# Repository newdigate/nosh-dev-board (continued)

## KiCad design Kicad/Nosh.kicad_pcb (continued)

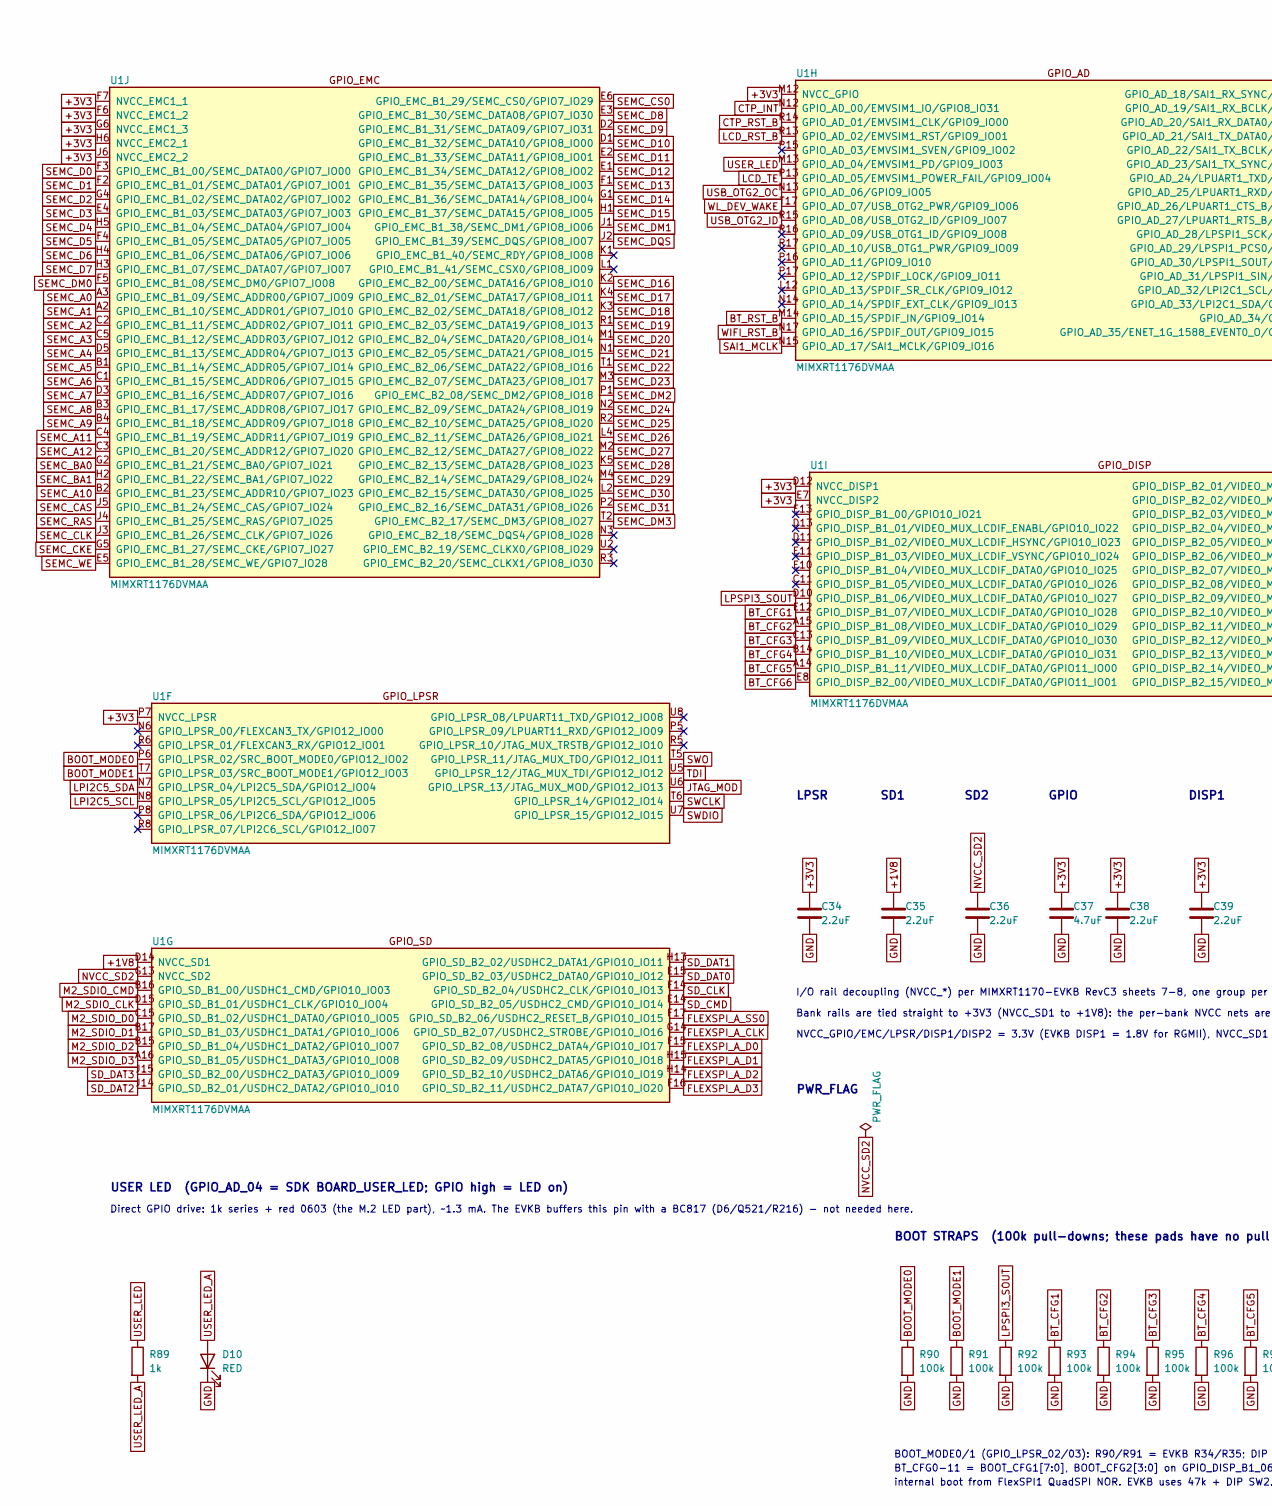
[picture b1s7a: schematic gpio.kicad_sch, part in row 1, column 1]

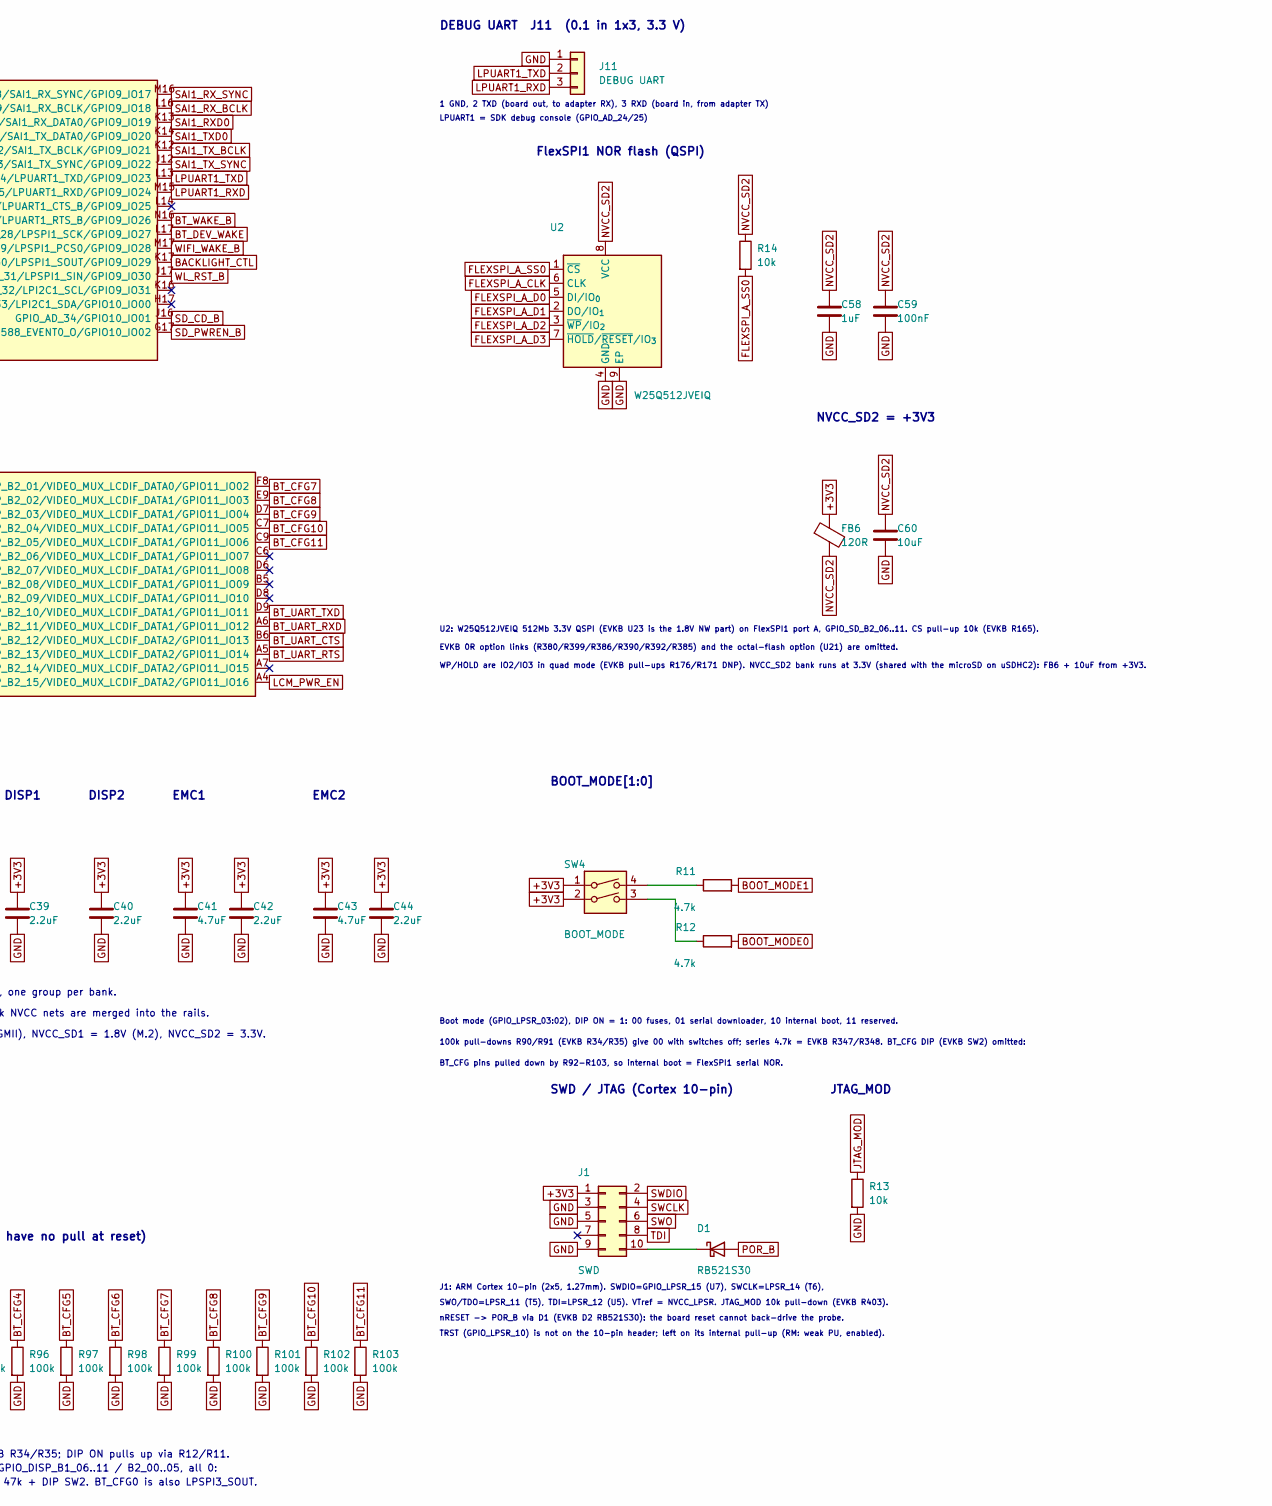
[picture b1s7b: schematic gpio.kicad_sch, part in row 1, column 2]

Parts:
C34, C35, C36, C38, C42, C44: 2.2uF; C_0402_1005Metric_ViP; MPN CL05A225MQ5NSNC; LCSC C12530
C37: 4.7uF; C_0402_1005Metric_ViP; MPN CL05A475MP5NRNC; LCSC C23733
C39, C40: 2.2uF; C_0402_1005Metric_JLC; MPN CL05A225MQ5NSNC; LCSC C12530
C41, C43: 4.7uF; C_0402_1005Metric_JLC; MPN CL05A475MP5NRNC; LCSC C23733
C58: 1uF; C_0402_1005Metric_JLC; MPN CL05A105KA5NQNC; LCSC C52923
C59: 100nF; C_0402_1005Metric_JLC; MPN CL05B104KO5NNNC; LCSC C1525
C60: 10uF; C_0603_1608Metric; MPN CL10A106KP8NNNC; LCSC C19702
D1: RB521S30; D_SOD-523; MPN RB521S30T1G; LCSC C145179
D10: RED; LED_0603_1608Metric; MPN KT-0603R; LCSC C2286
FB6: 120R; L_0402_1005Metric; MPN BLM15AG121SN1D; LCSC C85812
J1: SWD; PinHeader_2x05_P1.27mm_Vertical_SMD; MPN 20021121-00010C4LF; LCSC C150517
J11: DEBUG UART; PinHeader_1x03_P2.54mm_Vertical; MPN PZ254V-11-03P; LCSC C2937625
R11, R12: 4.7k; R_0402_1005Metric_JLC; MPN 0402WGF4701TCE; LCSC C25900
R13, R14: 10k; R_0402_1005Metric_JLC; MPN 0402WGF1002TCE; LCSC C25744
R89: 1k; R_0402_1005Metric_JLC; MPN 0402WGF1001TCE; LCSC C11702
R90, R91, R92, R93, R94, R95, R96, R97, R98, R99, R100, R101, R102, R103: 100k; R_0402_1005Metric_JLC; MPN 0402WGF1003TCE; LCSC C25741
SW4: BOOT_MODE; SW_DIP_SPSTx02_Slide_KingTek_DSHP02TS_W7.62mm_P1.27mm; MPN DSHP02TSGER; LCSC C3293142
U1: MIMXRT1176DVMAA; MAPBGA-289_14x14mm_Layout17x17_P0.8mm; MPN MIMXRT1176DVMAA; LCSC C1020237
U2: W25Q512JVEIQ; WSON-8-1EP_8x6mm_P1.27mm_EP3.4x4.3mm; MPN W25Q512JVEIQ; LCSC C7389628

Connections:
+1V8: C35.1, U1.D14 (NVCC_SD1); also elsewhere on the board
+3V3: C34.1, C37.1, C38.1, C39.1, C40.1, C41.1, C42.1, C43.1, C44.1, FB6.1, J1.1, SW4.1, SW4.2, U1.D12 (NVCC_DISP1), U1.E7 (NVCC_DISP2), U1.F6 (NVCC_EMC1_2), U1.F7 (NVCC_EMC1_1), U1.G6 (NVCC_EMC1_3), U1.H6 (NVCC_EMC2_1), U1.J6 (NVCC_EMC2_2), U1.M12 (NVCC_GPIO), U1.P7 (NVCC_LPSR); also elsewhere on the board
BACKLIGHT_CTL: U1.K17 (GPIO_AD_30/LPSPI1_SOUT/GPIO9_IO29); also elsewhere on the board
BOOT_MODE0: R12.2, R90.1, U1.P6 (GPIO_LPSR_02/SRC_BOOT_MODE0/GPIO12_IO02)
BOOT_MODE1: R11.2, R91.1, U1.T7 (GPIO_LPSR_03/SRC_BOOT_MODE1/GPIO12_IO03)
BT_CFG1: R93.1, U1.E12 (GPIO_DISP_B1_07/VIDEO_MUX_LCDIF_DATA0/G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)
BT_CFG2: R94.1, U1.A15 (GPIO_DISP_B1_08/VIDEO_MUX_LCDIF_DATA0/G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)
BT_CFG3: R95.1, U1.C13 (GPIO_DISP_B1_09/VIDEO_MUX_LCDIF_DATA0/G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)
BT_CFG4: R96.1, U1.B14 (GPIO_DISP_B1_10/VIDEO_MUX_LCDIF_DATA0/G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)
BT_CFG5: R97.1, U1.A14 (GPIO_DISP_B1_11/VIDEO_MUX_LCDIF_DATA0/G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)
BT_CFG6: R98.1, U1.E8 (GPIO_DISP_B2_00/VIDEO_MUX_LCDIF_DATA0/G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)
BT_CFG7: R99.1, U1.F8 (GPIO_DISP_B2_01/VIDEO_MUX_LCDIF_DATA0/G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)
BT_CFG8: R100.1, U1.E9 (GPIO_DISP_B2_02/VIDEO_MUX_LCDIF_DATA1/G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)
BT_CFG9: R101.1, U1.D7 (GPIO_DISP_B2_03/VIDEO_MUX_LCDIF_DATA1/G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)
BT_CFG10: R102.1, U1.C7 (GPIO_DISP_B2_04/VIDEO_MUX_LCDIF_DATA1/G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)
BT_CFG11: R103.1, U1.C9 (GPIO_DISP_B2_05/VIDEO_MUX_LCDIF_DATA1/G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)
BT_DEV_WAKE: U1.L17 (GPIO_AD_28/LPSPI1_SCK/GPIO9_IO27); also elsewhere on the board
BT_RST_B: U1.M14 (GPIO_AD_15/SPDIF_IN/GPIO9_IO14); also elsewhere on the board
BT_UART_CTS: U1.B6 (GPIO_DISP_B2_12/VIDEO_MUX_LCDIF_DATA2/G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); also elsewhere on the board
BT_UART_RTS: U1.A5 (GPIO_DISP_B2_13/VIDEO_MUX_LCDIF_DATA2/G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); also elsewhere on the board
BT_UART_RXD: U1.A6 (GPIO_DISP_B2_11/VIDEO_MUX_LCDIF_DATA1/G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); also elsewhere on the board
BT_UART_TXD: U1.D9 (GPIO_DISP_B2_10/VIDEO_MUX_LCDIF_DATA1/G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); also elsewhere on the board
BT_WAKE_B: U1.N16 (GPIO_AD_27/LPUART1_RTS_B/GPIO9_IO26); also elsewhere on the board
CTP_INT: U1.N12 (GPIO_AD_00/EMVSIM1_IO/GPIO8_IO31); also elsewhere on the board
CTP_RST_B: U1.R14 (GPIO_AD_01/EMVSIM1_CLK/GPIO9_IO00); also elsewhere on the board
FLEXSPI_A_CLK: U1.G14 (GPIO_SD_B2_07/USDHC2_STROBE/GPIO10_IO16), U2.6 (CLK)
FLEXSPI_A_D0: U1.F15 (GPIO_SD_B2_08/USDHC2_DATA4/GPIO10_IO17), U2.5 (DI/IO_{0})
FLEXSPI_A_D1: U1.H15 (GPIO_SD_B2_09/USDHC2_DATA5/GPIO10_IO18), U2.2 (DO/IO_{1})
FLEXSPI_A_D2: U1.H14 (GPIO_SD_B2_10/USDHC2_DATA6/GPIO10_IO19), U2.3 (~WP/IO_{2})
FLEXSPI_A_D3: U1.F16 (GPIO_SD_B2_11/USDHC2_DATA7/GPIO10_IO20), U2.7 (~HOLD/~RESET/IO_{3})
FLEXSPI_A_SS0: R14.2, U1.F17 (GPIO_SD_B2_06/USDHC2_RESET_B/GPIO10_IO15), U2.1 (~CS)
GND: C34.2, C35.2, C36.2, C37.2, C38.2, C39.2, C40.2, C41.2, C42.2, C43.2, C44.2, C58.2, C59.2, C60.2, D10.1 (K), J1.3, J1.5, J1.9, J11.1, R13.2, R90.2, R91.2, R92.2, R93.2, R94.2, R95.2, R96.2, R97.2, R98.2, R99.2, R100.2, R101.2, R102.2, R103.2, U2.4 (GND), U2.9 (EP); also elsewhere on the board
JTAG_MOD: R13.1, U1.U6 (GPIO_LPSR_13/JTAG_MUX_MOD/GPIO12_IO13)
LCD_RST_B: U1.R13 (GPIO_AD_02/EMVSIM1_RST/GPIO9_IO01); also elsewhere on the board
LCD_TE: U1.P13 (GPIO_AD_05/EMVSIM1_POWER_FAIL/GPIO9_IO04); also elsewhere on the board
LCM_PWR_EN: U1.A4 (GPIO_DISP_B2_15/VIDEO_MUX_LCDIF_DATA2/G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); also elsewhere on the board
LPI2C5_SCL: U1.N8 (GPIO_LPSR_05/LPI2C5_SCL/GPIO12_IO05); also elsewhere on the board
LPI2C5_SDA: U1.N7 (GPIO_LPSR_04/LPI2C5_SDA/GPIO12_IO04); also elsewhere on the board
LPSPI3_SOUT: R92.1, U1.D10 (GPIO_DISP_B1_06/VIDEO_MUX_LCDIF_DATA0/G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)
LPUART1_RXD: J11.3, U1.M15 (GPIO_AD_25/LPUART1_RXD/GPIO9_IO24)
LPUART1_TXD: J11.2, U1.L13 (GPIO_AD_24/LPUART1_TXD/GPIO9_IO23)
M2_SDIO_CLK: U1.D15 (GPIO_SD_B1_01/USDHC1_CLK/GPIO10_IO04); also elsewhere on the board
M2_SDIO_CMD: U1.B16 (GPIO_SD_B1_00/USDHC1_CMD/GPIO10_IO03); also elsewhere on the board
M2_SDIO_D0: U1.C15 (GPIO_SD_B1_02/USDHC1_DATA0/GPIO10_IO05); also elsewhere on the board
M2_SDIO_D1: U1.B17 (GPIO_SD_B1_03/USDHC1_DATA1/GPIO10_IO06); also elsewhere on the board
M2_SDIO_D2: U1.B15 (GPIO_SD_B1_04/USDHC1_DATA2/GPIO10_IO07); also elsewhere on the board
M2_SDIO_D3: U1.A16 (GPIO_SD_B1_05/USDHC1_DATA3/GPIO10_IO08); also elsewhere on the board
NVCC_SD2: C36.1, C58.1, C59.1, C60.1, FB6.2, R14.1, U1.G13 (NVCC_SD2), U2.8 (VCC); also elsewhere on the board
unnamed: D1.1 (K), J1.10
unnamed: R11.1, SW4.4
unnamed: R12.1, SW4.3
POR_B: D1.2 (A); also elsewhere on the board
SAI1_MCLK: U1.N15 (GPIO_AD_17/SAI1_MCLK/GPIO9_IO16); also elsewhere on the board
SAI1_RXD0: U1.K13 (GPIO_AD_20/SAI1_RX_DATA0/GPIO9_IO19); also elsewhere on the board
SAI1_RX_BCLK: U1.L16 (GPIO_AD_19/SAI1_RX_BCLK/GPIO9_IO18); also elsewhere on the board
SAI1_RX_SYNC: U1.M16 (GPIO_AD_18/SAI1_RX_SYNC/GPIO9_IO17); also elsewhere on the board
SAI1_TXD0: U1.K14 (GPIO_AD_21/SAI1_TX_DATA0/GPIO9_IO20); also elsewhere on the board
SAI1_TX_BCLK: U1.K12 (GPIO_AD_22/SAI1_TX_BCLK/GPIO9_IO21); also elsewhere on the board
SAI1_TX_SYNC: U1.J12 (GPIO_AD_23/SAI1_TX_SYNC/GPIO9_IO22); also elsewhere on the board
SD_CD_B: U1.J16 (GPIO_AD_34/GPIO10_IO01); also elsewhere on the board
SD_CLK: U1.F14 (GPIO_SD_B2_04/USDHC2_CLK/GPIO10_IO13); also elsewhere on the board
SD_CMD: U1.E14 (GPIO_SD_B2_05/USDHC2_CMD/GPIO10_IO14); also elsewhere on the board
SD_DAT0: U1.E15 (GPIO_SD_B2_03/USDHC2_DATA0/GPIO10_IO12); also elsewhere on the board
SD_DAT1: U1.H13 (GPIO_SD_B2_02/USDHC2_DATA1/GPIO10_IO11); also elsewhere on the board
SD_DAT2: U1.J14 (GPIO_SD_B2_01/USDHC2_DATA2/GPIO10_IO10); also elsewhere on the board
SD_DAT3: U1.J15 (GPIO_SD_B2_00/USDHC2_DATA3/GPIO10_IO09); also elsewhere on the board
SD_PWREN_B: U1.G17 (GPIO_AD_35/ENET_1G_1588_EVENT0_O/GPIO10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); also elsewhere on the board
SEMC_A0: U1.A3 (GPIO_EMC_B1_09/SEMC_ADDR00/GPIO7_IO09); also elsewhere on the board
SEMC_A1: U1.A2 (GPIO_EMC_B1_10/SEMC_ADDR01/GPIO7_IO10); also elsewhere on the board
SEMC_A2: U1.C2 (GPIO_EMC_B1_11/SEMC_ADDR02/GPIO7_IO11); also elsewhere on the board
SEMC_A3: U1.C5 (GPIO_EMC_B1_12/SEMC_ADDR03/GPIO7_IO12); also elsewhere on the board
SEMC_A4: U1.D5 (GPIO_EMC_B1_13/SEMC_ADDR04/GPIO7_IO13); also elsewhere on the board
SEMC_A5: U1.B1 (GPIO_EMC_B1_14/SEMC_ADDR05/GPIO7_IO14); also elsewhere on the board
SEMC_A6: U1.C1 (GPIO_EMC_B1_15/SEMC_ADDR06/GPIO7_IO15); also elsewhere on the board
SEMC_A7: U1.D3 (GPIO_EMC_B1_16/SEMC_ADDR07/GPIO7_IO16); also elsewhere on the board
SEMC_A8: U1.B3 (GPIO_EMC_B1_17/SEMC_ADDR08/GPIO7_IO17); also elsewhere on the board
SEMC_A9: U1.B4 (GPIO_EMC_B1_18/SEMC_ADDR09/GPIO7_IO18); also elsewhere on the board
SEMC_A10: U1.B2 (GPIO_EMC_B1_23/SEMC_ADDR10/GPIO7_IO23); also elsewhere on the board
SEMC_A11: U1.C4 (GPIO_EMC_B1_19/SEMC_ADDR11/GPIO7_IO19); also elsewhere on the board
SEMC_A12: U1.C3 (GPIO_EMC_B1_20/SEMC_ADDR12/GPIO7_IO20); also elsewhere on the board
SEMC_BA0: U1.G2 (GPIO_EMC_B1_21/SEMC_BA0/GPIO7_IO21); also elsewhere on the board
SEMC_BA1: U1.H2 (GPIO_EMC_B1_22/SEMC_BA1/GPIO7_IO22); also elsewhere on the board
SEMC_CAS: U1.J5 (GPIO_EMC_B1_24/SEMC_CAS/GPIO7_IO24); also elsewhere on the board
SEMC_CKE: U1.G5 (GPIO_EMC_B1_27/SEMC_CKE/GPIO7_IO27); also elsewhere on the board
SEMC_CLK: U1.J3 (GPIO_EMC_B1_26/SEMC_CLK/GPIO7_IO26); also elsewhere on the board
SEMC_CS0: U1.E6 (GPIO_EMC_B1_29/SEMC_CS0/GPIO7_IO29); also elsewhere on the board
SEMC_D0: U1.F3 (GPIO_EMC_B1_00/SEMC_DATA00/GPIO7_IO00); also elsewhere on the board
SEMC_D1: U1.F2 (GPIO_EMC_B1_01/SEMC_DATA01/GPIO7_IO01); also elsewhere on the board
SEMC_D2: U1.G4 (GPIO_EMC_B1_02/SEMC_DATA02/GPIO7_IO02); also elsewhere on the board
SEMC_D3: U1.E4 (GPIO_EMC_B1_03/SEMC_DATA03/GPIO7_IO03); also elsewhere on the board
SEMC_D4: U1.H5 (GPIO_EMC_B1_04/SEMC_DATA04/GPIO7_IO04); also elsewhere on the board
SEMC_D5: U1.F4 (GPIO_EMC_B1_05/SEMC_DATA05/GPIO7_IO05); also elsewhere on the board
SEMC_D6: U1.H4 (GPIO_EMC_B1_06/SEMC_DATA06/GPIO7_IO06); also elsewhere on the board
SEMC_D7: U1.H3 (GPIO_EMC_B1_07/SEMC_DATA07/GPIO7_IO07); also elsewhere on the board
SEMC_D8: U1.E3 (GPIO_EMC_B1_30/SEMC_DATA08/GPIO7_IO30); also elsewhere on the board
SEMC_D9: U1.D2 (GPIO_EMC_B1_31/SEMC_DATA09/GPIO7_IO31); also elsewhere on the board
SEMC_D10: U1.D1 (GPIO_EMC_B1_32/SEMC_DATA10/GPIO8_IO00); also elsewhere on the board
SEMC_D11: U1.E2 (GPIO_EMC_B1_33/SEMC_DATA11/GPIO8_IO01); also elsewhere on the board
SEMC_D12: U1.E1 (GPIO_EMC_B1_34/SEMC_DATA12/GPIO8_IO02); also elsewhere on the board
SEMC_D13: U1.F1 (GPIO_EMC_B1_35/SEMC_DATA13/GPIO8_IO03); also elsewhere on the board
SEMC_D14: U1.G1 (GPIO_EMC_B1_36/SEMC_DATA14/GPIO8_IO04); also elsewhere on the board
SEMC_D15: U1.H1 (GPIO_EMC_B1_37/SEMC_DATA15/GPIO8_IO05); also elsewhere on the board
SEMC_D16: U1.K2 (GPIO_EMC_B2_00/SEMC_DATA16/GPIO8_IO10); also elsewhere on the board
SEMC_D17: U1.K4 (GPIO_EMC_B2_01/SEMC_DATA17/GPIO8_IO11); also elsewhere on the board
SEMC_D18: U1.K3 (GPIO_EMC_B2_02/SEMC_DATA18/GPIO8_IO12); also elsewhere on the board
SEMC_D19: U1.R1 (GPIO_EMC_B2_03/SEMC_DATA19/GPIO8_IO13); also elsewhere on the board
SEMC_D20: U1.M1 (GPIO_EMC_B2_04/SEMC_DATA20/GPIO8_IO14); also elsewhere on the board
SEMC_D21: U1.N1 (GPIO_EMC_B2_05/SEMC_DATA21/GPIO8_IO15); also elsewhere on the board
SEMC_D22: U1.T1 (GPIO_EMC_B2_06/SEMC_DATA22/GPIO8_IO16); also elsewhere on the board
SEMC_D23: U1.M3 (GPIO_EMC_B2_07/SEMC_DATA23/GPIO8_IO17); also elsewhere on the board
SEMC_D24: U1.N2 (GPIO_EMC_B2_09/SEMC_DATA24/GPIO8_IO19); also elsewhere on the board
SEMC_D25: U1.R2 (GPIO_EMC_B2_10/SEMC_DATA25/GPIO8_IO20); also elsewhere on the board
SEMC_D26: U1.L4 (GPIO_EMC_B2_11/SEMC_DATA26/GPIO8_IO21); also elsewhere on the board
SEMC_D27: U1.M2 (GPIO_EMC_B2_12/SEMC_DATA27/GPIO8_IO22); also elsewhere on the board
SEMC_D28: U1.K5 (GPIO_EMC_B2_13/SEMC_DATA28/GPIO8_IO23); also elsewhere on the board
SEMC_D29: U1.M4 (GPIO_EMC_B2_14/SEMC_DATA29/GPIO8_IO24); also elsewhere on the board
SEMC_D30: U1.L2 (GPIO_EMC_B2_15/SEMC_DATA30/GPIO8_IO25); also elsewhere on the board
SEMC_D31: U1.P2 (GPIO_EMC_B2_16/SEMC_DATA31/GPIO8_IO26); also elsewhere on the board
SEMC_DM0: U1.F5 (GPIO_EMC_B1_08/SEMC_DM0/GPIO7_IO08); also elsewhere on the board
SEMC_DM1: U1.J1 (GPIO_EMC_B1_38/SEMC_DM1/GPIO8_IO06); also elsewhere on the board
SEMC_DM2: U1.P1 (GPIO_EMC_B2_08/SEMC_DM2/GPIO8_IO18); also elsewhere on the board
SEMC_DM3: U1.T2 (GPIO_EMC_B2_17/SEMC_DM3/GPIO8_IO27); also elsewhere on the board
SEMC_DQS: U1.J2 (GPIO_EMC_B1_39/SEMC_DQS/GPIO8_IO07); also elsewhere on the board
SEMC_RAS: U1.J4 (GPIO_EMC_B1_25/SEMC_RAS/GPIO7_IO25); also elsewhere on the board
SEMC_WE: U1.E5 (GPIO_EMC_B1_28/SEMC_WE/GPIO7_IO28); also elsewhere on the board
SWCLK: J1.4, U1.T6 (GPIO_LPSR_14/GPIO12_IO14)
SWDIO: J1.2, U1.U7 (GPIO_LPSR_15/GPIO12_IO15)
SWO: J1.6, U1.T5 (GPIO_LPSR_11/JTAG_MUX_TDO/GPIO12_IO11)
TDI: J1.8, U1.U5 (GPIO_LPSR_12/JTAG_MUX_TDI/GPIO12_IO12)
USB_OTG2_ID: U1.R15 (GPIO_AD_08/USB_OTG2_ID/GPIO9_IO07); also elsewhere on the board
USB_OTG2_OC: U1.N13 (GPIO_AD_06/GPIO9_IO05); also elsewhere on the board
USER_LED: R89.1, U1.M13 (GPIO_AD_04/EMVSIM1_PD/GPIO9_IO03)
USER_LED_A: D10.2 (A), R89.2
WIFI_RST_B: U1.N17 (GPIO_AD_16/SPDIF_OUT/GPIO9_IO15); also elsewhere on the board
WIFI_WAKE_B: U1.M17 (GPIO_AD_29/LPSPI1_PCS0/GPIO9_IO28); also elsewhere on the board
WL_DEV_WAKE: U1.T17 (GPIO_AD_07/USB_OTG2_PWR/GPIO9_IO06); also elsewhere on the board
WL_RST_B: U1.J17 (GPIO_AD_31/LPSPI1_SIN/GPIO9_IO30); also elsewhere on the board

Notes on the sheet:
DISP1
TRST (GPIO_LPSR_10) is not on the 10-pin header; left on its internal pull-up (RM: weak PU, enabled).
J1: ARM Cortex 10-pin (2x5, 1.27mm). SWDIO=GPIO_LPSR_15 (U7), SWCLK=LPSR_14 (T6),
SWD / JTAG (Cortex 10-pin)
EMC1
NVCC_SD2 = +3V3
LPUART1 = SDK debug console (GPIO_AD_24/25)
FlexSPI1 NOR flash (QSPI)
nRESET -> POR_B via D1 (EVKB D2 RB521S30): the board reset cannot back-drive the probe.
SD1
BOOT STRAPS (100k pull-downs; these pads have no pull at reset)
I/O rail decoupling (NVCC_*) per MIMXRT1170-EVKB RevC3 sheets 7-8, one group per bank.
NVCC_GPIO/EMC/LPSR/DISP1/DISP2 = 3.3V (EVKB DISP1 = 1.8V for RGMII), NVCC_SD1 = 1.8V (M.2), NVCC_SD2 = 3.3V.
PWR_FLAG
SD2
100k pull-downs R90/R91 (EVKB R34/R35) give 00 with switches off; series 4.7k = EVKB R347/R348. BT_CFG DIP (EVKB SW2) omitted:
Direct GPIO drive: 1k series + red 0603 (the M.2 LED part), ~1.3 mA. The EVKB buffers this pin with a BC817 (D6/Q521/R216) - not needed here.
DISP2
internal boot from FlexSPI1 QuadSPI NOR. EVKB uses 47k + DIP SW2. BT_CFG0 is also LPSPI3_SOUT.
USER LED (GPIO_AD_04 = SDK BOARD_USER_LED; GPIO high = LED on)
BT_CFG0-11 = BOOT_CFG1[7:0], BOOT_CFG2[3:0] on GPIO_DISP_B1_06..11 / B2_00..05, all 0:
Boot mode (GPIO_LPSR_03:02), DIP ON = 1: 00 fuses, 01 serial downloader, 10 internal boot, 11 reserved.
GPIO
Bank rails are tied straight to +3V3 (NVCC_SD1 to +1V8): the per-bank NVCC nets are merged into the rails.
EVKB 0R option links (R380/R399/R386/R390/R392/R385) and the octal-flash option (U21) are omitted.
WP/HOLD are IO2/IO3 in quad mode (EVKB pull-ups R176/R171 DNP). NVCC_SD2 bank runs at 3.3V (shared with the microSD on uSDHC2): FB6 + 10uF from +3V3.
BOOT_MODE[1:0]
1 GND, 2 TXD (board out, to adapter RX), 3 RXD (board in, from adapter TX)
LPSR
DEBUG UART J11 (0.1 in 1x3, 3.3 V)
EMC2
JTAG_MOD
BT_CFG pins pulled down by R92-R103, so internal boot = FlexSPI1 serial NOR.
U2: W25Q512JVEIQ 512Mb 3.3V QSPI (EVKB U23 is the 1.8V NW part) on FlexSPI1 port A, GPIO_SD_B2_06..11. CS pull-up 10k (EVKB R165).
BOOT_MODE0/1 (GPIO_LPSR_02/03): R90/R91 = EVKB R34/R35; DIP ON pulls up via R12/R11.
SWO/TDO=LPSR_11 (T5), TDI=LPSR_12 (U5). VTref = NVCC_LPSR. JTAG_MOD 10k pull-down (EVKB R403).

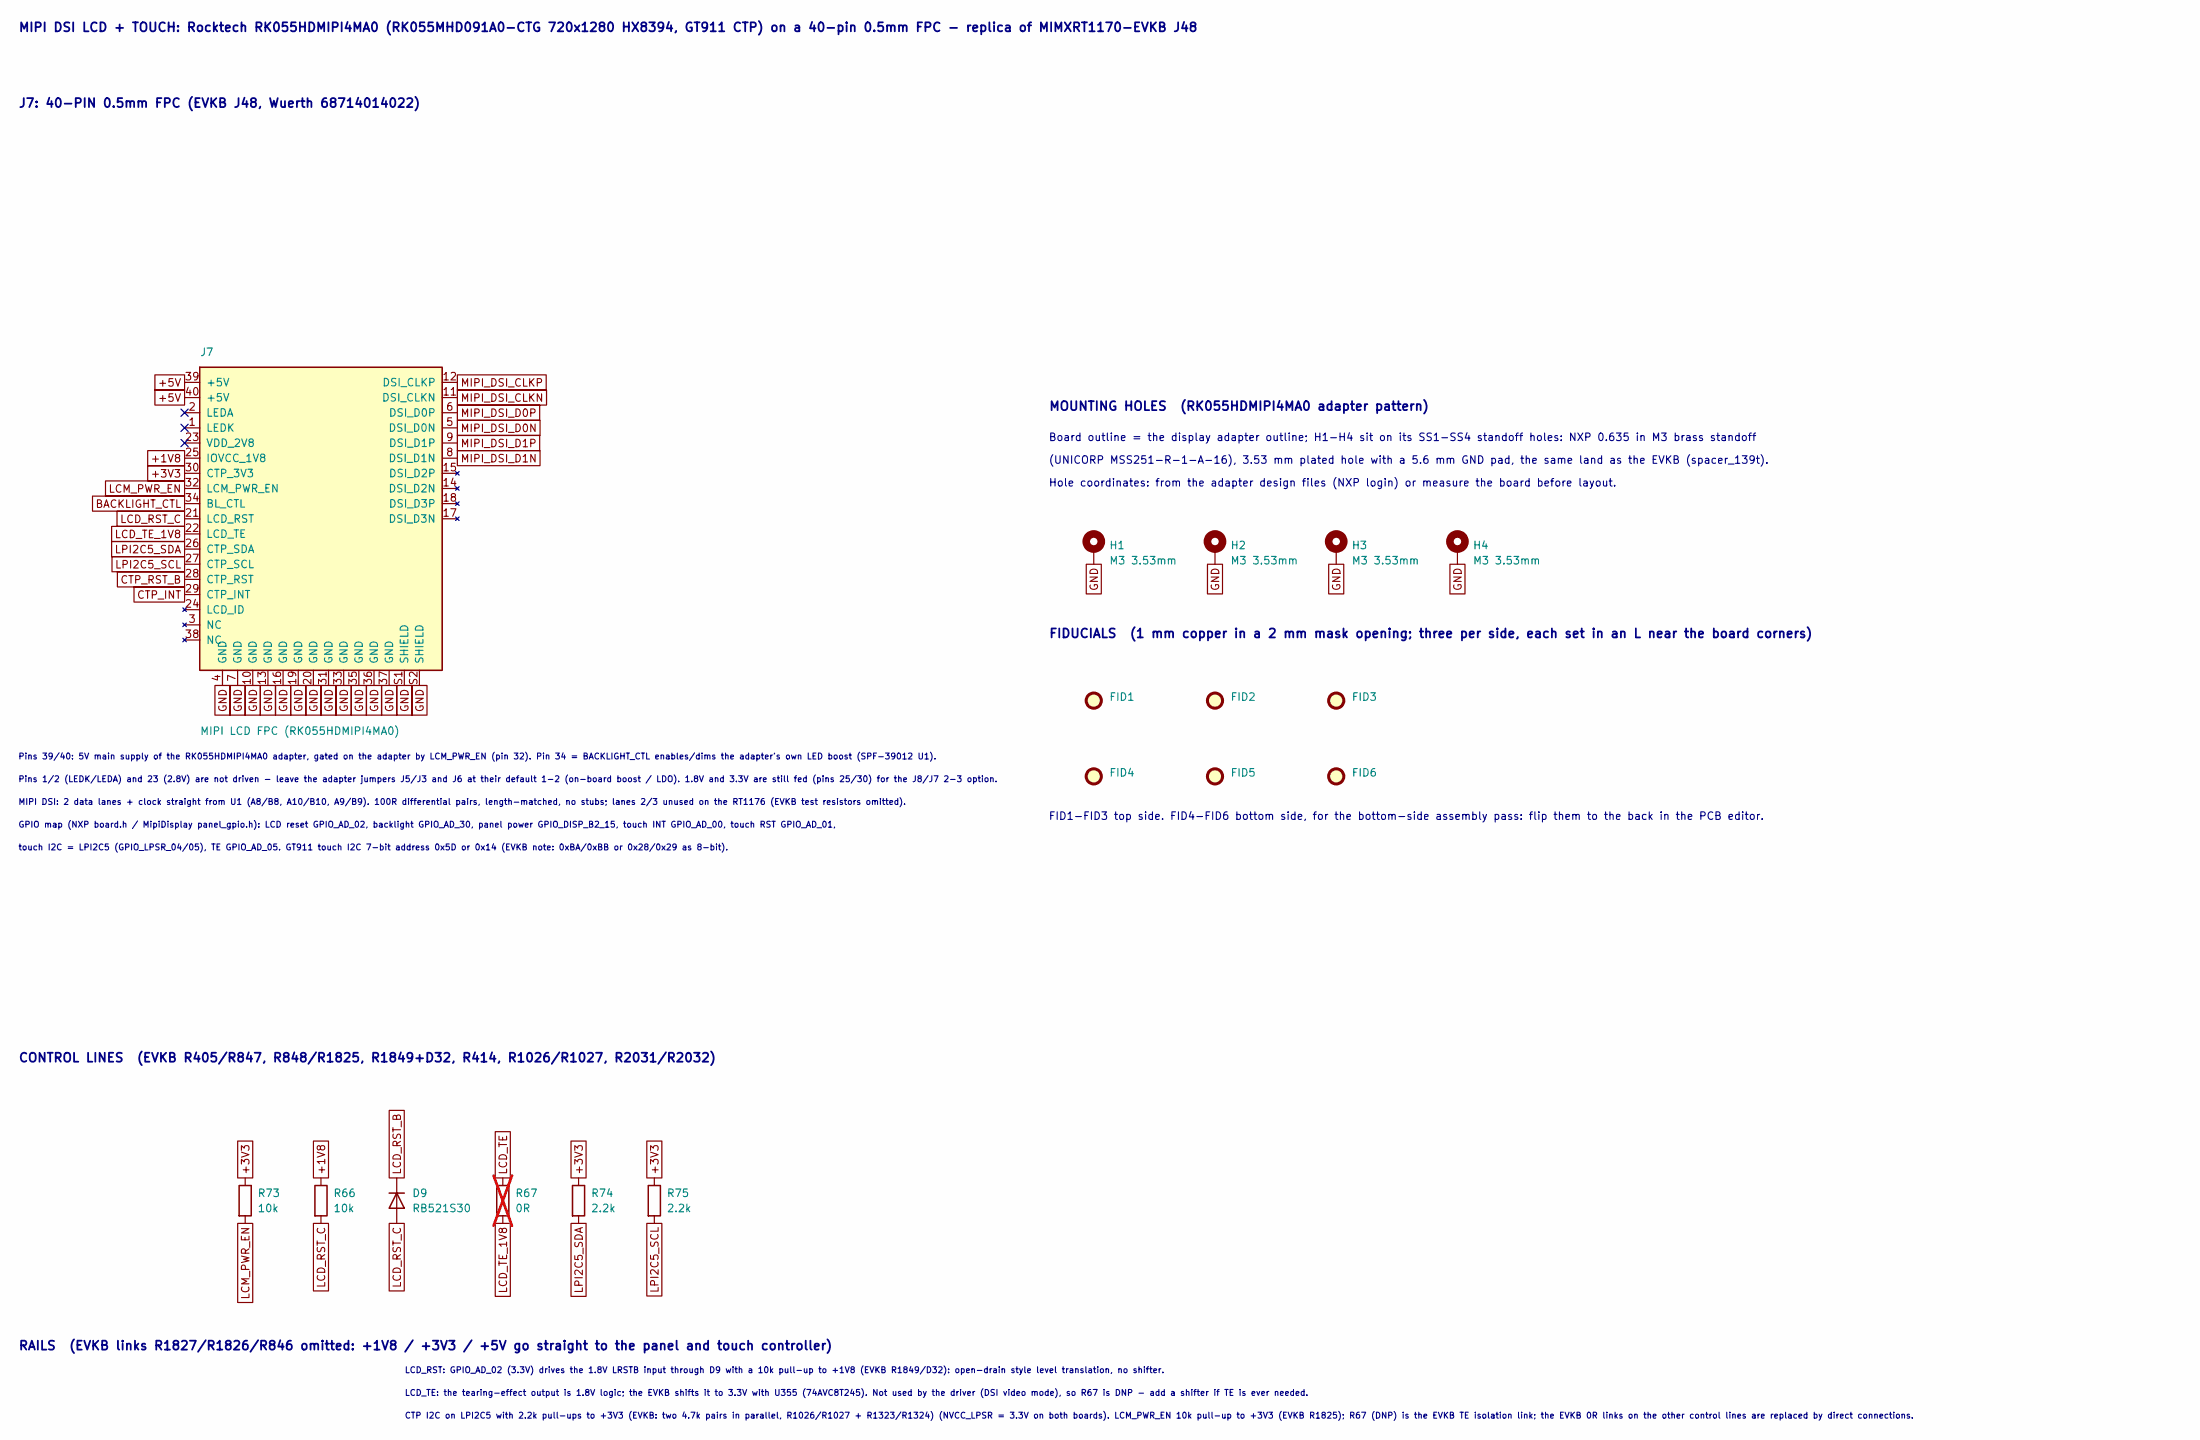
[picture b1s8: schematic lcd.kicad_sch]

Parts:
D9: RB521S30; D_SOD-523; MPN RB521S30T1G; LCSC C145179
FID1, FID2, FID3, FID4, FID5, FID6: Fiducial; Fiducial_1mm_Mask2mm
H1, H2, H3, H4: M3 3.53mm; MountingHole_3.53mm_M3_Pad
J7: MIPI LCD FPC (RK055HDMIPI4MA0); FPC40_0p5_Wuerth_68714014022; MPN 68714014022; LCSC C6264899
R66, R73: 10k; R_0402_1005Metric_JLC; MPN 0402WGF1002TCE; LCSC C25744
R67: 0R; R_0402_1005Metric_JLC; MPN 0402WGF0000TCE; LCSC C17168; not fitted
R74, R75: 2.2k; R_0402_1005Metric_JLC; MPN 0402WGF2201TCE; LCSC C25879

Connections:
+1V8: J7.25 (IOVCC_1V8), R66.1; also elsewhere on the board
+3V3: J7.30 (CTP_3V3), R73.1, R74.1, R75.1; also elsewhere on the board
+5V: J7.39 (+5V), J7.40 (+5V); also elsewhere on the board
BACKLIGHT_CTL: J7.34 (BL_CTL); also elsewhere on the board
CTP_INT: J7.29 (CTP_INT); also elsewhere on the board
CTP_RST_B: J7.28 (CTP_RST); also elsewhere on the board
GND: H1.1, H2.1, H3.1, H4.1, J7.4 (GND), J7.7 (GND), J7.10 (GND), J7.13 (GND), J7.16 (GND), J7.19 (GND), J7.20 (GND), J7.31 (GND), J7.33 (GND), J7.35 (GND), J7.36 (GND), J7.37 (GND), J7.S1 (SHIELD), J7.S2 (SHIELD); also elsewhere on the board
LCD_RST_B: D9.1 (K); also elsewhere on the board
LCD_RST_C: D9.2 (A), J7.21 (LCD_RST), R66.2
LCD_TE: R67.1; also elsewhere on the board
LCD_TE_1V8: J7.22 (LCD_TE), R67.2
LCM_PWR_EN: J7.32 (LCM_PWR_EN), R73.2; also elsewhere on the board
LPI2C5_SCL: J7.27 (CTP_SCL), R75.2; also elsewhere on the board
LPI2C5_SDA: J7.26 (CTP_SDA), R74.2; also elsewhere on the board
MIPI_DSI_CLKN: J7.11 (DSI_CLKN); also elsewhere on the board
MIPI_DSI_CLKP: J7.12 (DSI_CLKP); also elsewhere on the board
MIPI_DSI_D0N: J7.5 (DSI_D0N); also elsewhere on the board
MIPI_DSI_D0P: J7.6 (DSI_D0P); also elsewhere on the board
MIPI_DSI_D1N: J7.8 (DSI_D1N); also elsewhere on the board
MIPI_DSI_D1P: J7.9 (DSI_D1P); also elsewhere on the board

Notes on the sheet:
J7: 40-PIN 0.5mm FPC (EVKB J48, Wuerth 68714014022)
MIPI DSI LCD + TOUCH: Rocktech RK055HDMIPI4MA0 (RK055MHD091A0-CTG 720x1280 HX8394, GT911 CTP) on a 40-pin 0.5mm FPC - replica of MIMXRT1170-EVKB J48
MIPI DSI: 2 data lanes + clock straight from U1 (A8/B8, A10/B10, A9/B9). 100R differential pairs, length-matched, no stubs; lanes 2/3 unused on the RT1176 (EVKB test resistors omitted).
touch I2C = LPI2C5 (GPIO_LPSR_04/05), TE GPIO_AD_05. GT911 touch I2C 7-bit address 0x5D or 0x14 (EVKB note: 0xBA/0xBB or 0x28/0x29 as 8-bit).
LCD_TE: the tearing-effect output is 1.8V logic; the EVKB shifts it to 3.3V with U355 (74AVC8T245). Not used by the driver (DSI video mode), so R67 is DNP - add a shifter if TE is ever needed.
CTP I2C on LPI2C5 with 2.2k pull-ups to +3V3 (EVKB: two 4.7k pairs in parallel, R1026/R1027 + R1323/R1324) (NVCC_LPSR = 3.3V on both boards). LCM_PWR_EN 10k pull-up to +3V3 (EVKB R1825); R67 (DNP) is the EVKB TE isolation link; the EVKB 0R links on the other control lines are replaced by direct con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
(UNICORP MSS251-R-1-A-16), 3.53 mm plated hole with a 5.6 mm GND pad, the same land as the EVKB (spacer_139t).
CONTROL LINES (EVKB R405/R847, R848/R1825, R1849+D32, R414, R1026/R1027, R2031/R2032)
Hole coordinates: from the adapter design files (NXP login) or measure the board before layout.
RAILS (EVKB links R1827/R1826/R846 omitted: +1V8 / +3V3 / +5V go straight to the panel and touch controller)
FIDUCIALS (1 mm copper in a 2 mm mask opening; three per side, each set in an L near the board corners)
LCD_RST: GPIO_AD_02 (3.3V) drives the 1.8V LRSTB input through D9 with a 10k pull-up to +1V8 (EVKB R1849/D32): open-drain style level translation, no shifter.
MOUNTING HOLES (RK055HDMIPI4MA0 adapter pattern)
Pins 1/2 (LEDK/LEDA) and 23 (2.8V) are not driven - leave the adapter jumpers J5/J3 and J6 at their default 1-2 (on-board boost / LDO). 1.8V and 3.3V are still fed (pins 25/30) for the J8/J7 2-3 option.
FID1-FID3 top side. FID4-FID6 bottom side, for the bottom-side assembly pass: flip them to the back in the PCB editor.
Board outline = the display adapter outline; H1-H4 sit on its SS1-SS4 standoff holes: NXP 0.635 in M3 brass standoff
GPIO map (NXP board.h / MipiDisplay panel_gpio.h): LCD reset GPIO_AD_02, backlight GPIO_AD_30, panel power GPIO_DISP_B2_15, touch INT GPIO_AD_00, touch RST GPIO_AD_01,
Pins 39/40: 5V main supply of the RK055HDMIPI4MA0 adapter, gated on the adapter by LCM_PWR_EN (pin 32). Pin 34 = BACKLIGHT_CTL enables/dims the adapter's own LED boost (SPF-39012 U1).

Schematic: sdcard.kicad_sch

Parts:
C115: 18pF; C_0402_1005Metric_JLC; MPN 0402CG180J500NT; LCSC C1549; not fitted
C116: 220nF; C_0402_1005Metric_JLC; MPN CL05B224KO5NNNC; LCSC C16772
C117: 1uF; C_0402_1005Metric_JLC; MPN CL05A105KA5NQNC; LCSC C52923
C118: 2.2uF; C_0402_1005Metric_JLC; MPN CL05A225MQ5NSNC; LCSC C12530
C119: 100nF; C_0402_1005Metric_JLC; MPN CL05B104KO5NNNC; LCSC C1525
D13, D14, D15, D16, D17, D18: TPD1E05U06; ESD_X1SON-2_0.6x1mm_JLC; MPN TPD1E05U06DPYR; LCSC C436349
J5: microSD; microSD_HC_Hirose_DM3AT-SF-PEJM5_JLC; MPN DM3AT-SF-PEJM5; LCSC C114218
Q3: IRLML6401; SOT-23; MPN IRLML6401TRPBF; LCSC C3034
R53, R54, R57, R59, R108, R109: 10k; R_0402_1005Metric_JLC; MPN 0402WGF1002TCE; LCSC C25744
R55: 100k; R_0402_1005Metric_JLC; MPN 0402WGF1003TCE; LCSC C25741
R56: 0R; R_0402_1005Metric_JLC; MPN 0402WGF0000TCE; LCSC C17168
R58, R60: 1k; R_0402_1005Metric_JLC; MPN 0402WGF1001TCE; LCSC C11702

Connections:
+3V3: Q3.2 (S), R57.1; also elsewhere on the board
GND: C115.2, C116.2, C117.2, C118.2, C119.2, D13.2 (GND), D14.2 (GND), D15.2 (GND), D16.2 (GND), D17.2 (GND), D18.2 (GND), J5.6 (VSS), J5.9 (DET_B), J5.SH (SHIELD), R55.2, R59.2, R60.2; also elsewhere on the board
NVCC_SD2: R53.1, R54.1, R108.1, R109.1; also elsewhere on the board
SD_CD_B: J5.10 (DET_A), R57.2; also elsewhere on the board
SD_CLK: R56.1; also elsewhere on the board
SD_CLK_C: C115.1, D13.1 (I/O), J5.5 (CLK), R56.2
SD_CMD: D14.1 (I/O), J5.3 (CMD), R53.2; also elsewhere on the board
SD_DAT0: D15.1 (I/O), J5.7 (DAT0), R54.2; also elsewhere on the board
SD_DAT1: D16.1 (I/O), J5.8 (DAT1), R108.2; also elsewhere on the board
SD_DAT2: D17.1 (I/O), J5.1 (DAT2), R109.2; also elsewhere on the board
SD_DAT3: D18.1 (I/O), J5.2 (DAT3/CD), R55.1; also elsewhere on the board
SD_PWREN_B: R58.1; also elsewhere on the board
SD_PWR_G: C116.1, Q3.1 (G), R58.2, R59.1
VSD_3V3: C117.1, C118.1, C119.1, J5.4 (VDD), Q3.3 (D), R60.1

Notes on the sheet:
The SD2 bank (NVCC_SD2) is 3.3V, shared with the FlexSPI flash (now the 3.3V W25Q512JVEIQ): default-speed / high-speed only, no UHS-I 1.8V signalling.
VSD_3V3 power switch (SD_PWREN_B = GPIO_AD_35, active low; P-FET on by default)
microSD on uSDHC2 (GPIO_SD_B2_00..05: DATA3, DATA2, DATA1, DATA0, CLK, CMD), its own bus - the EVKB shares uSDHC1 between the M.2 socket and J15.
Per EVKB sheets 5/11: 10k pull-ups on CMD/DAT0, 100k DAT3 pull-down, 0R CLK series with DNP 18pF cap (EVKB C247), IRLML6401 high-side switch (10k/1k/0.22uF), 1uF+2.2uF+0.1uF, 1k bleed.
microSD SOCKET (uSDHC2, 3.3V, Hirose DM3AT push-push)
Card detect: socket switch DET_A to GND, DET_B -> SD_CD_B (10k pull-up) -> GPIO_AD_34 (the native USDHC2_CD_B pad is taken by SDRAM D17). Card inserted = low.
Pull-ups / CLK series / card detect
ESD on the microSD lines: TPD1E05U06 (5.5 V, 0.42 pF) on each line, placed on the trace next to J5.

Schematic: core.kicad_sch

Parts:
C47, C48, C50: 1uF; C_0402_1005Metric_ViP; MPN CL05A105KA5NQNC; LCSC C52923
C49, C51, C52: 1uF; C_0402_1005Metric_JLC; MPN CL05A105KA5NQNC; LCSC C52923
C53, C54: 4.7pF; C_0402_1005Metric_JLC; MPN CC0402BRNPO9BN4R7; LCSC C325453
FB3, FB4, FB5: 120R; L_0402_1005Metric; MPN BLM15AG121SN1D; LCSC C85812
U1: MIMXRT1176DVMAA; MAPBGA-289_14x14mm_Layout17x17_P0.8mm; MPN MIMXRT1176DVMAA; LCSC C1020237
Y1: 24MHz; Crystal_SMD_2016-4Pin_2.0x1.6mm; MPN XRCGB24M000F2P91R0; LCSC C5250251

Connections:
+1V8: FB3.1, FB5.1; also elsewhere on the board
+3V3: FB4.1; also elsewhere on the board
GND: C47.2, C48.2, C49.2, C50.2, C51.2, C52.2, C53.2, C54.2, Y1.2 (G), Y1.4 (G); also elsewhere on the board
MIPI_DSI_CLKN: U1.A9 (MIPI_DSI_CKN); also elsewhere on the board
MIPI_DSI_CLKP: U1.B9 (MIPI_DSI_CKP); also elsewhere on the board
MIPI_DSI_D0N: U1.A8 (MIPI_DSI_DN0); also elsewhere on the board
MIPI_DSI_D0P: U1.B8 (MIPI_DSI_DP0); also elsewhere on the board
MIPI_DSI_D1N: U1.A10 (MIPI_DSI_DN1); also elsewhere on the board
MIPI_DSI_D1P: U1.B10 (MIPI_DSI_DP1); also elsewhere on the board
unnamed: C53.1, U1.U16 (XTALI), Y1.1
unnamed: C54.1, U1.T16 (XTALO), Y1.3
USB1_DN: U1.E16 (USB1_DN); also elsewhere on the board
USB1_DP: U1.E17 (USB1_DP); also elsewhere on the board
USB1_VBUS: C51.1, U1.D17 (USB1_VBUS); also elsewhere on the board
USB2_DN: U1.C16 (USB2_DN); also elsewhere on the board
USB2_DP: U1.C17 (USB2_DP); also elsewhere on the board
USB2_VBUS: C52.1, U1.D16 (USB2_VBUS); also elsewhere on the board
VDDA_1P0: C50.1, U1.F10 (VDD_MIPI_1P0); also elsewhere on the board
VDD_MIPI_1P8: C49.1, FB5.2, U1.F9 (VDD_MIPI_1P8)
VDD_USB_1P8: C47.1, FB3.2, U1.H12 (VDD_USB_1P8)
VDD_USB_3P3: C48.1, FB4.2, U1.G12 (VDD_USB_3P3)

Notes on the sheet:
USB2_VBUS
VDD_MIPI_1P0 is fed directly from the internal VDDA_1P0 LDO output (one net, VDDA_1P0). VBUS caps are the EVKB C252/C251.
PWR_FLAG
USB/MIPI supply decoupling per MIMXRT1170-EVKB RevC3 sheet 8 (C270/C244/C119/C272, L30/L31/L32, R1848).
PWR_FLAG: remove once a regulator output drives the rail.
MIPI_1P8
Y1: EVKB Y4 (NXP 230-78313), 2.0x1.6mm 4-pad; 4.7pF load caps per EVKB C316/C317. EVKB R189 (DNP feedback) omitted.
USB1_VBUS
USB_1P8
MIPI_1P0
USB_3P3
24 MHz
